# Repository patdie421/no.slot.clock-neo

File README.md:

# no.slot.clock-neo

v2.1 Tested in an Apple IIe (europa motherboard) and works fine. Other version will be tested soon.  

Use the DS1215 DIP chip and readily available through-hole components  at a reasonable price (except for the DS1215 :-( ).  

This PCB is is functionally equivalent to the DS1216 E/F (cf. https://github.com/patdie421/no.slot.clock-neo/blob/main/resources/DS1216.PDF).  

Modern driver available in this repository : https://github.com/a2stuff/prodos-drivers  

other resources :  

* Reactive micro "no slot clock" : https://wiki.reactivemicro.com/No-Slot_Clock ($$$)  
* An other PCB with smd components : https://www.xpmtl.net/wordpress/apple-ii/no-slot-clock/  (pcb design not found, but nice job)  
* Original driver source code : https://gist.github.com/mgcaret/ae2860c754fd029d2640107c4fe0bffd  
* Original user manual : https://mirrors.apple2.org.za/Apple%20II%20Documentation%20Project/Chips/SMT%20No-Slot%20Clock/Manuals/No-Slot%20Clock%20-%20Manual.pdf  
* Original software : https://mirrors.apple2.org.za/Apple%20II%20Documentation%20Project/Chips/SMT%20No-Slot%20Clock/Disk%20Images/

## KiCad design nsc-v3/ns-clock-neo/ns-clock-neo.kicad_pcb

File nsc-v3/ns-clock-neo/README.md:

Designed for the Apple IIc 4100 equipped with a memory expansion card. Allows the NSC to be positioned under the card.

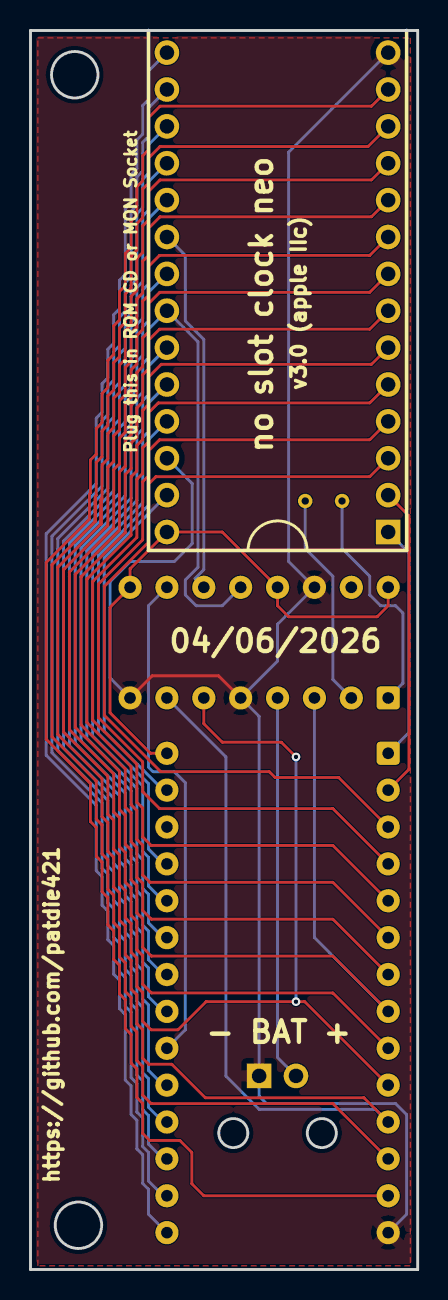
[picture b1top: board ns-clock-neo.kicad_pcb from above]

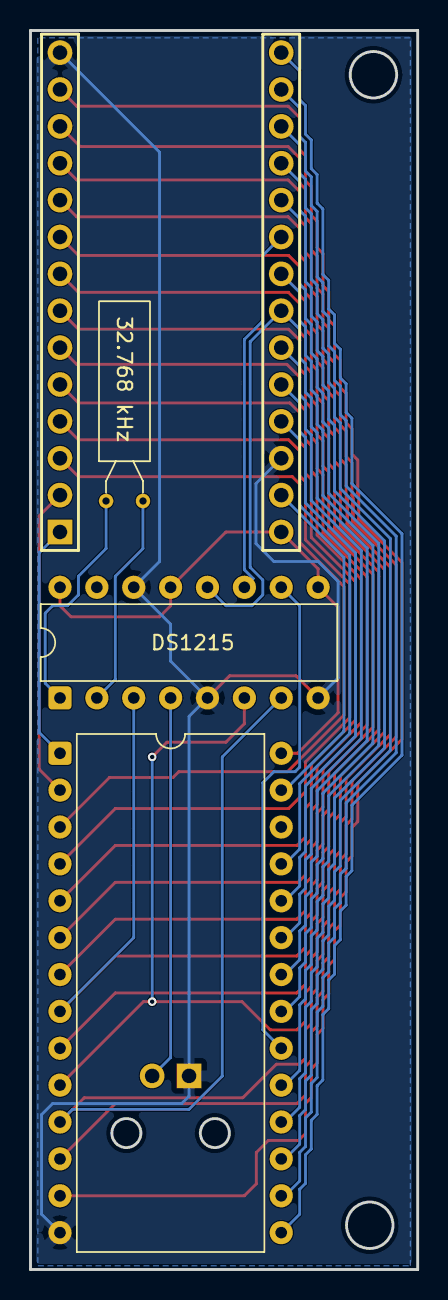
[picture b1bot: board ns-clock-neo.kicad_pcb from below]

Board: 2 copper layers, 26.7 x 85.3 mm, 6 parts (2 on the bottom side), 31 nets.

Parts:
DS1215: DIP-16_W7.62mm
J2: Bat connector; PinHeader_1x02_P2.54mm_Horizontal
J3, J4: Conn_01x14_Pin; PinHeader_1x14_P2.54mm_Vertical
U1: 2764; DIP-28_W15.24mm
Y1: 32.768 kHz; Crystal_AT310_D3.0mm_L10.0mm_Horizontal

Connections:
+3V0: DS1215.4 (BAT1), J2.2
+5V: DS1215.9 (ROM/~RAM), DS1215.13 (~RST), DS1215.16 (VCCI), J4.1, U1.28 (VCC)
A0: DS1215.6 (D), J3.10, U1.10 (A0)
A1: J3.9, U1.9 (A1)
A2: DS1215.3 (~WE), J3.8, U1.8 (A2)
A3: J3.7, U1.7 (A3)
A4: J3.6, U1.6 (A4)
A5: J3.5, U1.5 (A5)
A6: J3.4, U1.4 (A6)
A7: J3.3, U1.3 (A7)
A8: J4.4, U1.25 (A8)
A9: J4.5, U1.24 (A9)
A10: J4.8, U1.21 (A10)
A11: J4.6, U1.23 (A11)
A12: J3.2, U1.2 (A12)
CE: DS1215.10 (~CEO), U1.20 (~CE)
CEI: DS1215.11 (~CEI), J4.9
D0: DS1215.7 (Q), J3.11, U1.11 (D0)
D1: J3.12, U1.12 (D1)
D2: J3.13, U1.13 (D2)
D3: J4.14, U1.15 (D3)
D4: J4.13, U1.16 (D4)
D5: J4.12, U1.17 (D5)
D6: J4.11, U1.18 (D6)
D7: J4.10, U1.19 (D7)
GND: DS1215.5 (GND), DS1215.8 (GND), DS1215.14 (BAT2), J2.1, J3.14, J4.3, U1.14 (GND)
unnamed: DS1215.1 (X1), Y1.1
unnamed: DS1215.2 (X2), Y1.2
OE: DS1215.12 (~OE), J4.7, U1.22 (~OE)
PGM: J4.2, U1.27 (~PGM)
VPP: J3.1, U1.1 (VPP)

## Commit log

2026-05-10 Add project title to README.md
2026-05-10 Rename IMG_3976.HEIC to no.slot.clock.png
2026-05-10 Rename DS1215.PDF to DS1215.PDF
2026-05-10 Add reference to DS1216F and prodos-drivers
2026-05-10 Add link to DS1216 PDF in README
    Updated README to include a link to the DS1216 PDF.
2026-05-10 Add driver and resource links to README
2026-05-15 Rename IMG_3976.jpeg to images/NSC03.jpeg
